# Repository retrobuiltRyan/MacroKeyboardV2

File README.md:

# MacroKeyboardV2
13-Key Arduino ProMicro USB Macro Keyboard
https://youtu.be/IDlcxLQ1SbY?si=J5Tzyvr0lGsu_4_Y

Trouble Shooting Tips and FAQs
Some basic trouble shooting:

 1. This PCB is not plug-and-play. You have to upload at least the example code linked from this product description. Code is on this page.
 2. Use the Arduino IDE to program. (see arduino.cc for help with adding libraries and getting the software to program the Arduino).
 3. Make sure you have these libraries added:
 4. Make sure the Arduino Micro 32u4 is selected when programming this board. Tools> Board> Arduino Micro.

Go to Tools>Manage Libraries.

2) Make sure you have the Arduino Pro Micro selected. Tools> Board> Arduino Micro

5. Make sure all the solder jumpers are soldered! You’ll get really weird results (phantom keys) if you miss a jumper.

6. You may have to hold down the reset button, hit upload sketch, wait for the IDE to try to ‘upload’ to the Arduino, then release the reset button.
The boot-loader for uploading is a short window in the Arduino Pro Micro. The Pro Micro wants to default to the USB HID mode. Catching the short window for uploading a program might take a few tries; i.e to get a feel for the timing (my experience).
Search for these libraries. When you find the library listed below, install it.
7. DO NOT SOLDER BOTH I2C power jumpers. Solder only one!
8. 

Eagle CAD files include (9.2.x) I have abondoned EagleCAD for KiCAD. KiCAD can import Eagle design files; happy macro-ing!

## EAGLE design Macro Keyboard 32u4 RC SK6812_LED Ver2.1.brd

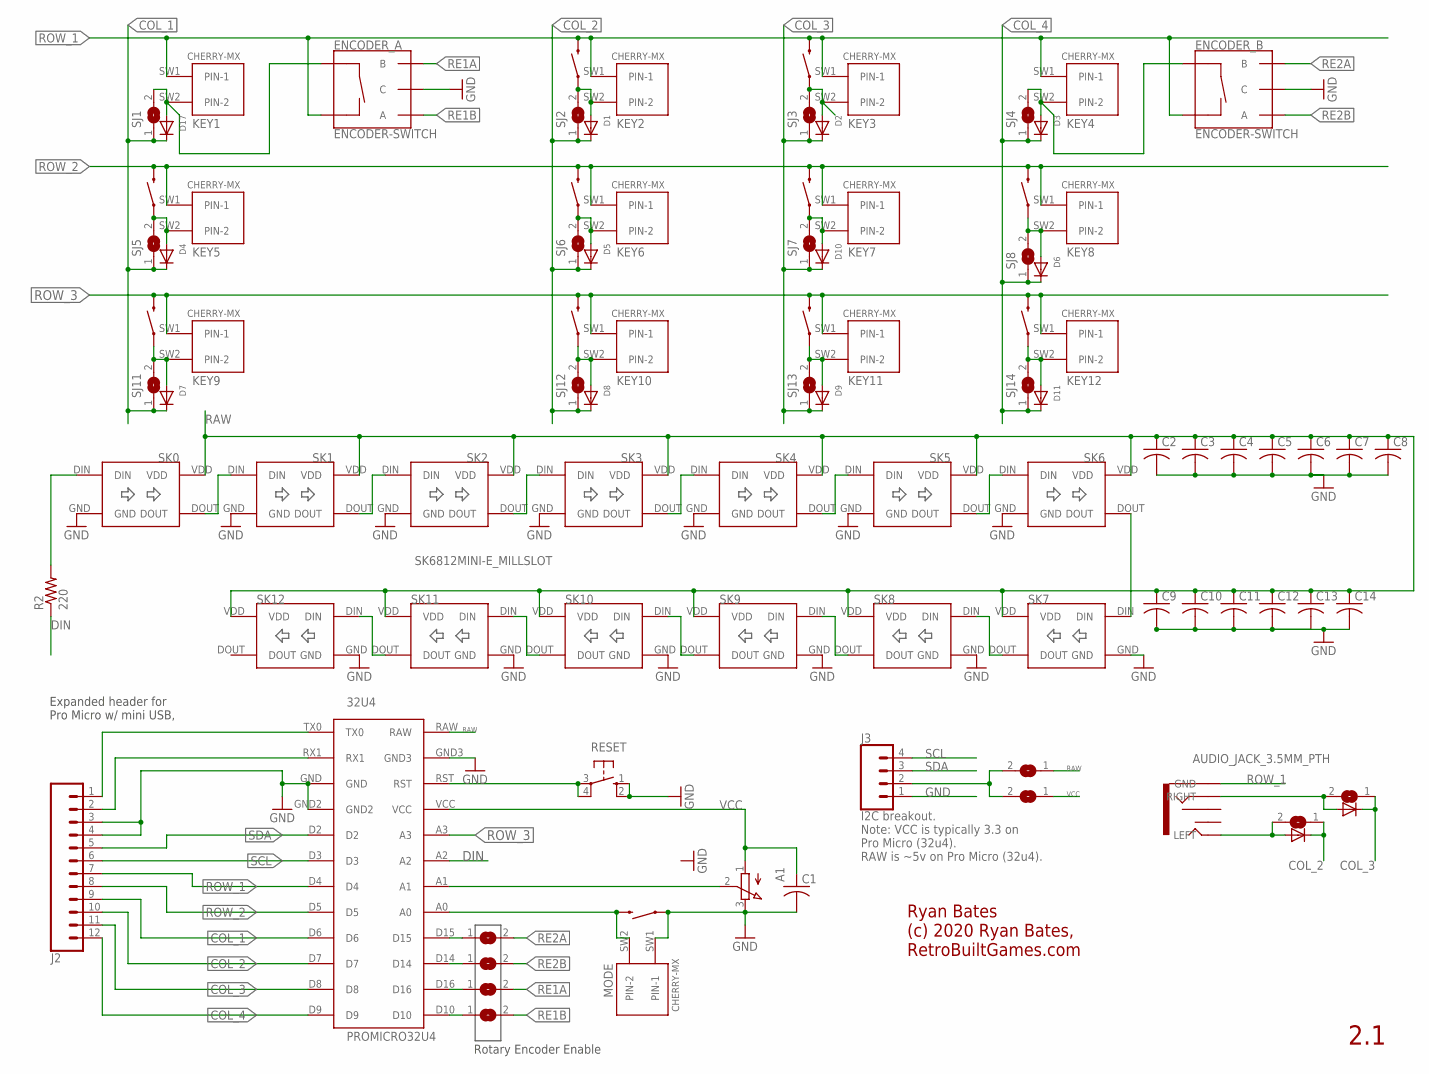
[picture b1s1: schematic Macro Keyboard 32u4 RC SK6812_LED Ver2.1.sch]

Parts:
32U4: PROMICRO32U4
A1: 3RP/1610N
C1: C-USC1206; C1206
C2, C3, C4, C5, C6, C7, C8, C9, C10, C11, C12, C13, C14: C-USC0805K; C0805K
D1, D2, D3, D4, D5, D6, D7, D8, D9, D10, D11, D15, D16, D17: DIODESOD-123; SOD-123
ENCODER_A: ENCODER-SWITCH; ROTARY_ENC_PLAIN
ENCODER_B: ENCODER-SWITCH; ROTARY_ENC_PLAIN
J1: AUDIO_JACK_3.5MM_PTH; AUDIO-JACK
J2: CONN_12NO_SILK; 1X12_NO_SILK
J3: CONN_041X04_NO_SILK; 1X04_NO_SILK
KEY1, KEY2, KEY3, KEY4, KEY5, KEY6, KEY7, KEY8, KEY9, KEY10, KEY11, KEY12: CHERRY-MX
MODE: CHERRY-MX
R2: 220; M1206
RESET: 10-XX; B3F-10XX
S1, S2, S3, S4, S5, S6, S7, S8, S9, S10, S11: MOMENTARY-SWITCH-SPST-PTH-12MM; TACTILE_SWITCH_PTH_12MM
SJ1, SJ2, SJ3, SJ4, SJ5, SJ6, SJ7, SJ8, SJ9, SJ10, SJ11, SJ12, SJ13, SJ14, SJ16, SJ17, SJ18, SJ19, SJ20, SJ21: SJ
SK0, SK1, SK2, SK3, SK4, SK5, SK6, SK7, SK8, SK9, SK10, SK11, SK12: SK6812MINI-E_MILLSLOT

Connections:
COL_1: 32U4.D6, D4.C, D7.C, D17.C, J2.9, SJ1.1, SJ5.1, SJ11.1
COL_2: 32U4.D7, D1.C, D5.C, D8.C, D15.C, J2.10, SJ2.1, SJ6.1, SJ12.1, SJ16.1
COL_3: 32U4.D8, D2.C, D9.C, D10.C, D16.C, J2.11, SJ3.1, SJ7.1, SJ13.1, SJ17.1
COL_4: 32U4.D9, D3.C, D6.C, D11.C, J2.12, SJ4.1, SJ8.1, SJ14.1
DIN: 32U4.A2, R2.1
GND: 32U4.GND, 32U4.GND2, 32U4.GND3, A1.3 (E), C1.2, C2.2, C3.2, C4.2, C5.2, C6.2, C7.2, C8.2, C9.2, C10.2, C11.2, C12.2, C13.2, C14.2, ENCODER_A.C, ENCODER_B.C, J2.3, J2.4, J3.1, MODE.SW1 (PIN-1), RESET.1 (S), RESET.2 (S1), S11.1, SK0.GND, SK1.GND, SK2.GND, SK3.GND, SK4.GND, SK5.GND, SK6.GND, SK7.GND, SK8.GND, SK9.GND, SK10.GND, SK11.GND, SK12.GND
unnamed: 32U4.RX1, J2.2
unnamed: D1.A, KEY2.SW2 (PIN-2), S4.1, SJ2.2
unnamed: D4.A, KEY5.SW2 (PIN-2), S9.1, SJ5.2
unnamed: D5.A, KEY6.SW2 (PIN-2), S10.1, SJ6.2
unnamed: SK0.DOUT, SK1.DIN
unnamed: D3.A, ENCODER_B.SW+, KEY4.SW2 (PIN-2), SJ4.2
unnamed: D2.A, KEY3.SW2 (PIN-2), S3.1, SJ3.2
unnamed: D16.A, J1.RIGHT, SJ17.2
unnamed: 32U4.RST, RESET.3, RESET.4 (P1)
unnamed: 32U4.TX0, J2.1
unnamed: 32U4.A0, MODE.SW2 (PIN-2), S11.3 (2)
unnamed: SK1.DOUT, SK2.DIN
unnamed: SK2.DOUT, SK3.DIN
unnamed: D10.A, KEY7.SW2 (PIN-2), S1.1, SJ7.2
unnamed: R2.2, SK0.DIN
unnamed: D6.A, KEY8.SW2 (PIN-2), S2.1, SJ8.2
unnamed: D17.A, ENCODER_A.SW+, KEY1.SW2 (PIN-2), SJ1.2
unnamed: SK3.DOUT, SK4.DIN
unnamed: J3.2, SJ9.2, SJ10.2
unnamed: D7.A, KEY9.SW2 (PIN-2), S5.1, SJ11.2
unnamed: 32U4.A1, A1.2 (S)
unnamed: D9.A, KEY11.SW2 (PIN-2), S7.1, SJ13.2
unnamed: D8.A, KEY10.SW2 (PIN-2), S6.1, SJ12.2
unnamed: D11.A, KEY12.SW2 (PIN-2), S8.1, SJ14.2
unnamed: SK4.DOUT, SK5.DIN
unnamed: SK5.DOUT, SK6.DIN
unnamed: SK6.DOUT, SK7.DIN
unnamed: SK7.DOUT, SK8.DIN
unnamed: SK8.DOUT, SK9.DIN
unnamed: SK9.DOUT, SK10.DIN
unnamed: 32U4.D15, SJ18.1
unnamed: 32U4.D14, SJ19.1
unnamed: 32U4.D16, SJ20.1
unnamed: 32U4.D10, SJ21.1
unnamed: SK10.DOUT, SK11.DIN
unnamed: SK11.DOUT, SK12.DIN
unnamed: D15.A, J1.LEFT, SJ16.2
RAW: 32U4.RAW, C2.1, C3.1, C4.1, C5.1, C6.1, C7.1, C8.1, C9.1, C10.1, C11.1, C12.1, C13.1, C14.1, SJ9.1, SK0.VDD, SK1.VDD, SK2.VDD, SK3.VDD, SK4.VDD, SK5.VDD, SK6.VDD, SK7.VDD, SK8.VDD, SK9.VDD, SK10.VDD, SK11.VDD, SK12.VDD
RE1A: ENCODER_A.B, SJ20.2
RE1B: ENCODER_A.A, SJ21.2
RE2A: ENCODER_B.B, SJ18.2
RE2B: ENCODER_B.A, SJ19.2
ROW_1: 32U4.D4, ENCODER_A.SW-, ENCODER_B.SW-, J1.GND, J2.7, KEY1.SW1 (PIN-1), KEY2.SW1 (PIN-1), KEY3.SW1 (PIN-1), KEY4.SW1 (PIN-1), S3.3 (2), S4.3 (2)
ROW_2: 32U4.D5, J2.8, KEY5.SW1 (PIN-1), KEY6.SW1 (PIN-1), KEY7.SW1 (PIN-1), KEY8.SW1 (PIN-1), S1.3 (2), S2.3 (2), S9.3 (2), S10.3 (2)
ROW_3: 32U4.A3, KEY9.SW1 (PIN-1), KEY10.SW1 (PIN-1), KEY11.SW1 (PIN-1), KEY12.SW1 (PIN-1), S5.3 (2), S6.3 (2), S7.3 (2), S8.3 (2)
SCL: 32U4.D3, J2.6, J3.4
SDA: 32U4.D2, J2.5, J3.3
VCC: 32U4.VCC, A1.1 (A), C1.1, SJ10.1

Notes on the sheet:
Rotary Encoder Enable
2.1
Ryan Bates (c) 2020 Ryan Bates, RetroBuiltGames.com
Expanded header for Pro Micro w/ mini USB,
I2C breakout. Note: VCC is typically 3.3 on Pro Micro (32u4). RAW is ~5v on Pro Micro (32u4).

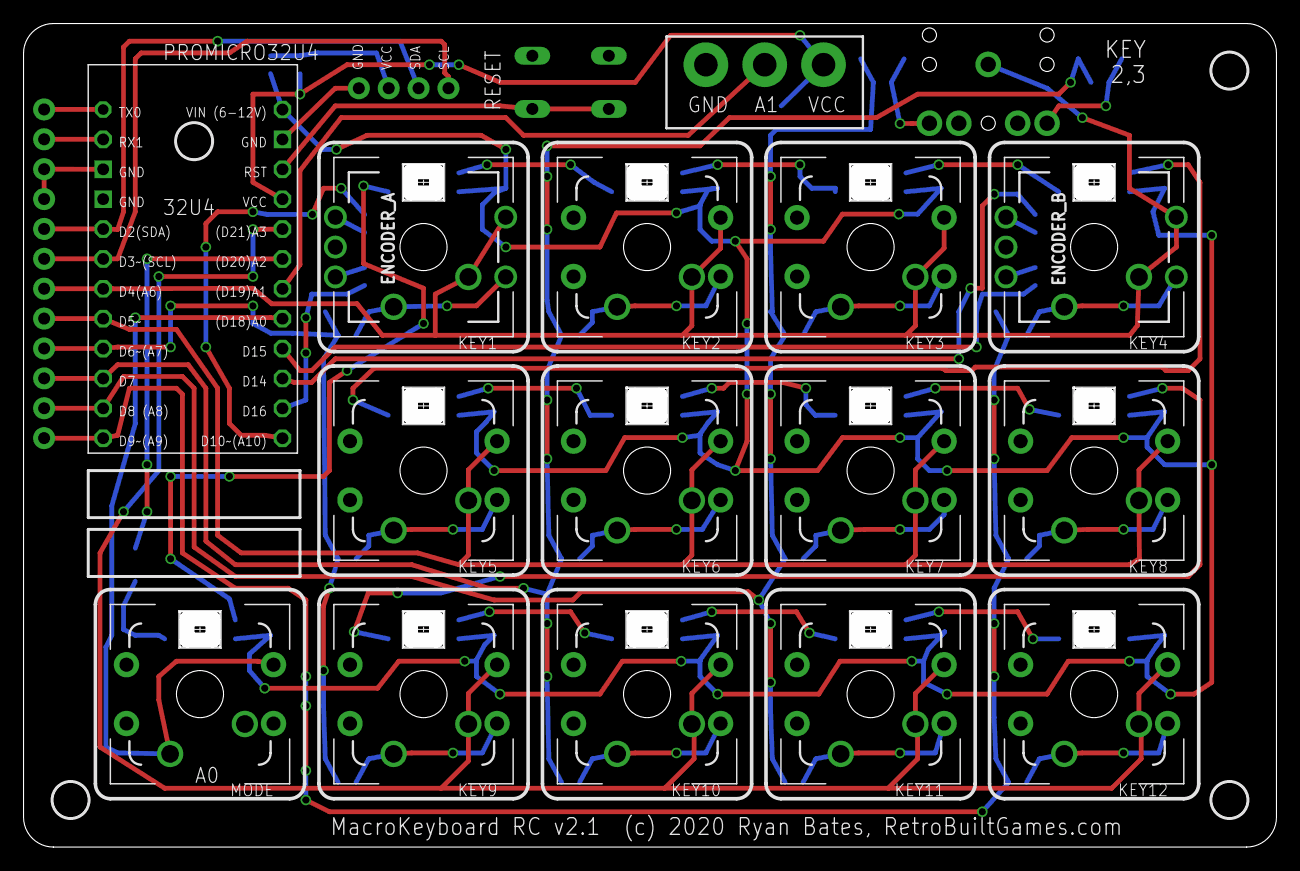
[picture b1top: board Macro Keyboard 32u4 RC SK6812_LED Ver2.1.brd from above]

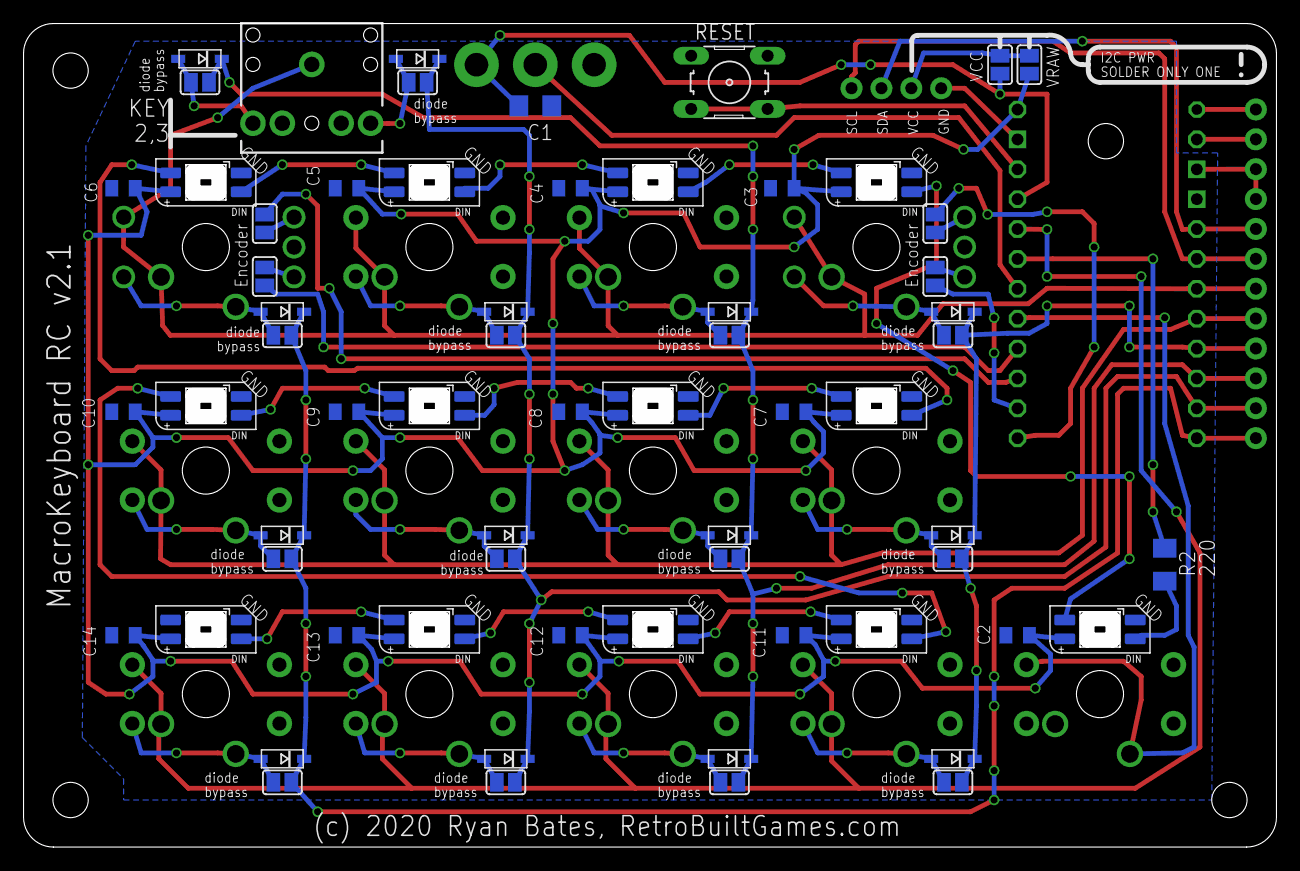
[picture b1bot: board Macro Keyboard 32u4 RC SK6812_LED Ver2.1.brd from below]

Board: 2 copper layers, 105.2 x 68.7 mm, 98 parts (51 on the bottom side), 54 nets.

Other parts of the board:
U$1, U$2, U$7, U$8: 3,0

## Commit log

2024-04-26 Create Simple Macros, LCD and RGB LED support
    A multi-mode Macro keyboard with Arduino Pro Micro using row column matrix.
    * This is a basic sketch to understand key layout, basic hotkeys macros and some extras like:
    * -RBG addressable LEDs compatible with Adafruit's neopixel library.
    * -i2c for 4x20 LCD to describe each function. (you might have a different LCD...)
    * -mouse movement + mouse clicks.
2024-04-26 Add files via upload
    EXPERT MACRO CODE EXAMPLE -FOR PR0 lvl KEYBOARD JOCKEYS ONLY
2024-09-09 PCB design files and GERBERs
    (EAGLE v9.x CAD schematic and board.
    GERBERS (the .zip file) were typically ordered from JLCPCB
2024-11-16 correct macro keyboard v2.1 files uploaded
2024-11-16 Delete MacroKeyboard Stream Deck plans (1).rar
    douplicate file
2024-11-16 Delete Macro Keyboard 32u4 RC Mini v1.0 JLCPCB.zip
    wrong file
2024-11-16 Delete Macro Keyboard 32u4 Row Column MiniMacro v1.0.sch
    wrong file
2024-11-16 Delete Macro Keyboard 32u4 Row Column MiniMacro v1.0.brd
    wrong file
2024-11-16 Update README.md
    note about kiCAD

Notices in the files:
Macro Keyboard 32u4 RC SK6812_LED Ver2.1.brd:
MacroKeyboard RC v2.1  (c) 2020 Ryan Bates, RetroBuiltGames.com
parts and their libraries:
SparkFun-Switches: Licensing: Creative Commons ShareAlike 4.0 International - https://creativecommons.org/licenses/by-sa/4.0
